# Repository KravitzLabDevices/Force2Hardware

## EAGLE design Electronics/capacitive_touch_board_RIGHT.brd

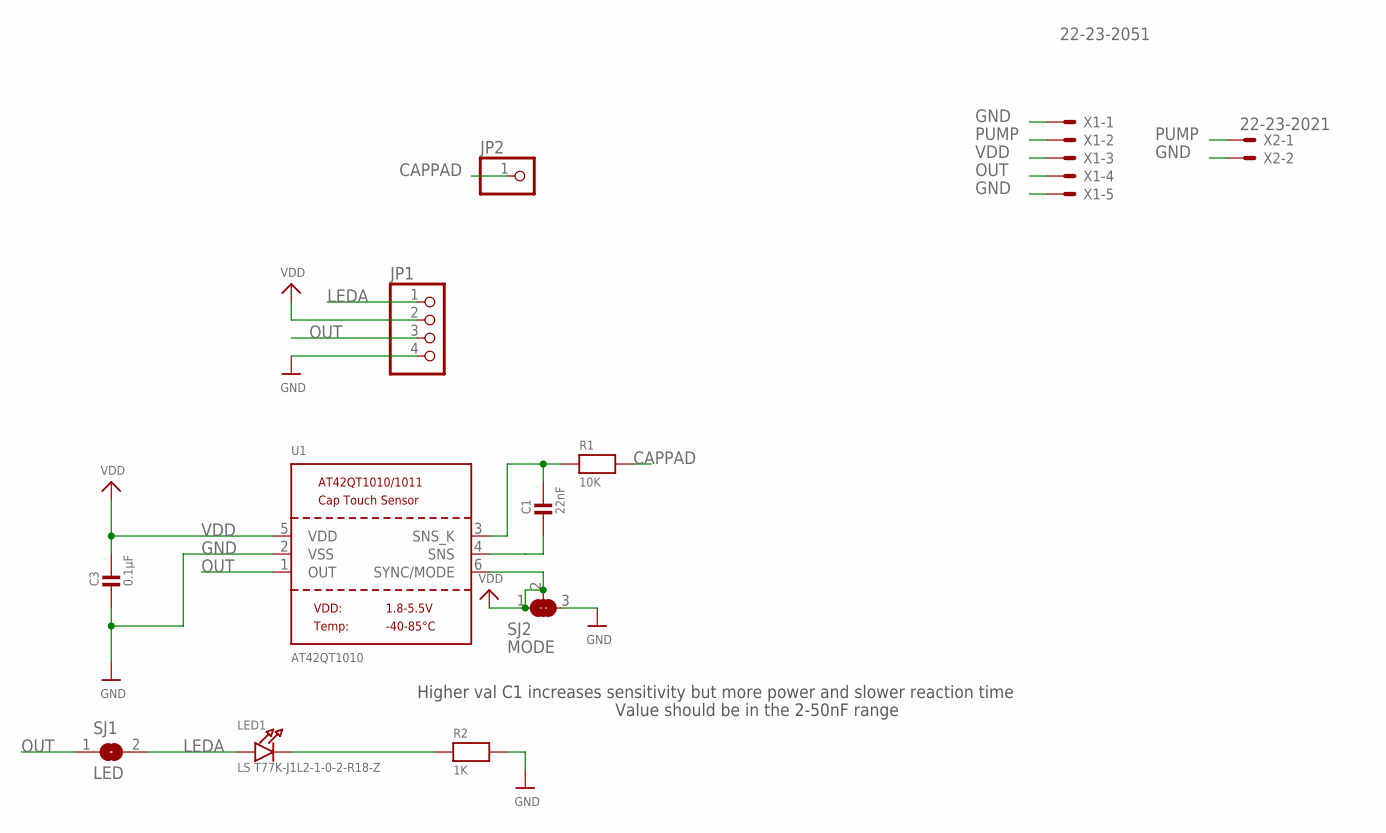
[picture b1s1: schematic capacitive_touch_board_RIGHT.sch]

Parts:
C1: 22nF; _0805
C3: 0.1µF; _0805
JP1: HEADER-1X476MIL; 1X04_ROUND_76
JP2: PINHD-1X1; 1X01
LED1: LS T77K-J1L2-1-0-2-R18-Z; PLCC2_REVMOUNT
R1: 10K; _0805
R2: 1K; _0805
SJ1: LED; SOLDERJUMPER_CLOSEDWIRE
SJ2: MODE; SOLDERJUMPER_2WAY_OPEN_NOPASTE
U1: AT42QT1010; SOT23-6
X1: 22-23-2051
X2: 22-23-2021

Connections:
CAPPAD: JP2.1, R1.2
GND: C3.2, JP1.4, R2.2, SJ2.3, U1.2 (VSS), X1.1, X1.5, X2.2
LEDA: JP1.1, LED1.A, SJ1.2
unnamed: C1.2, U1.4 (SNS)
unnamed: C1.1, R1.1, U1.3 (SNS_K)
unnamed: LED1.K (C), R2.1
OUT: JP1.3, SJ1.1, U1.1 (OUT), X1.4
PUMP: X1.2, X2.1
VDD: C3.1, JP1.2, SJ2.1, SJ2.2, U1.5 (VDD), U1.6 (SYNC/MODE), X1.3

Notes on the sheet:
Higher val C1 increases sensitivity but more power and slower reaction time
Value should be in the 2-50nF range

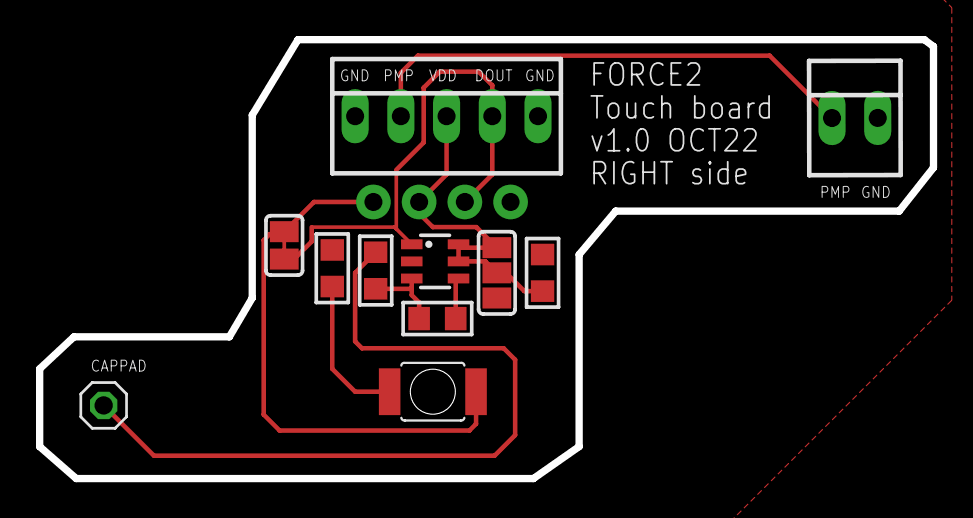
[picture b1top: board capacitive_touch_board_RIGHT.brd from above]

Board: 2 copper layers, 49.7 x 24.4 mm, 12 parts (0 on the bottom side), 9 nets.

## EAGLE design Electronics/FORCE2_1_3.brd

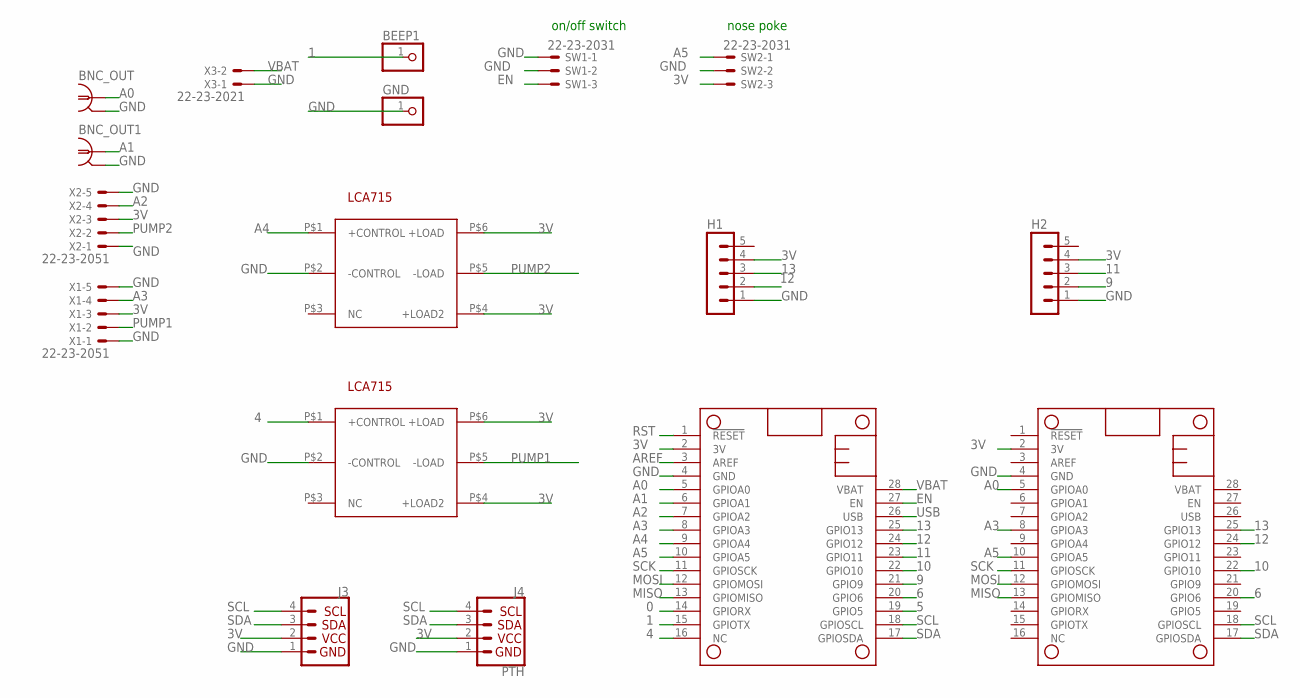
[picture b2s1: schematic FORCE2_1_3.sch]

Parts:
BEEP1: PINHD-1X1; 1X01
BNC_OUT, BNC_OUT1: 1-227161-0; AMP_227161
GND: PINHD-1X1; 1X01
H1, H2: MA05-1
J3: QWIIC_CONNECTORJS-1MM; 1X04_1MM_RA
J4: PTH; 1X04
MS1, MS2: MICROSHIELD_NODIM; MICROSHIELD_DIM
SSR2, SSR3: LCA715S; LCA7XX
SW1, SW2: 22-23-2031
X1, X2: 22-23-2051
X3: 22-23-2021

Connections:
0: MS2.14 (GPIORX)
1: BEEP1.1, MS2.15 (GPIOTX)
3V: H1.4, H2.4, J3.2, J4.2, MS1.2 (3V), MS2.2 (3V), SSR2.P$4 (+LOAD2), SSR2.P$6 (+LOAD), SSR3.P$4 (+LOAD2), SSR3.P$6 (+LOAD), SW2.3, X1.3, X2.3
4: MS2.16 (NC), SSR2.P$1 (+CONTROL)
5: MS2.19 (GPIO5)
6: MS1.20 (GPIO6), MS2.20 (GPIO6)
9: H2.2, MS2.21 (GPIO9)
10: MS1.22 (GPIO10), MS2.22 (GPIO10)
11: H2.3, MS2.23 (GPIO11)
12: H1.2, MS1.24 (GPIO12), MS2.24 (GPIO12)
13: H1.3, MS1.25 (GPIO13), MS2.25 (GPIO13)
A0: BNC_OUT.1, MS1.5 (GPIOA0), MS2.5 (GPIOA0)
A1: BNC_OUT1.1, MS2.6 (GPIOA1)
A2: MS2.7 (GPIOA2), X2.4
A3: MS1.8 (GPIOA3), MS2.8 (GPIOA3), X1.4
A4: MS2.9 (GPIOA4), SSR3.P$1 (+CONTROL)
A5: MS1.10 (GPIOA5), MS2.10 (GPIOA5), SW2.1
AREF: MS2.3 (AREF)
EN: MS2.27 (EN), SW1.3
GND: BNC_OUT.2, BNC_OUT1.2, GND.1, H1.1, H2.1, J3.1, J4.1, MS1.4 (GND), MS2.4 (GND), SSR2.P$2 (-CONTROL), SSR3.P$2 (-CONTROL), SW1.1, SW1.2, SW2.2, X1.1, X1.5, X2.1, X2.5, X3.1
MISO: MS1.13 (GPIOMISO), MS2.13 (GPIOMISO)
MOSI: MS1.12 (GPIOMOSI), MS2.12 (GPIOMOSI)
PUMP1: SSR2.P$5 (-LOAD), X1.2
PUMP2: SSR3.P$5 (-LOAD), X2.2
RST: MS2.1 (!RESET)
SCK: MS1.11 (GPIOSCK), MS2.11 (GPIOSCK)
SCL: J3.4, J4.4, MS1.18 (GPIOSCL), MS2.18 (GPIOSCL)
SDA: J3.3, J4.3, MS1.17 (GPIOSDA), MS2.17 (GPIOSDA)
USB: MS2.26 (USB)
VBAT: MS2.28 (VBAT), X3.2

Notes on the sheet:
nose poke
on/off switch

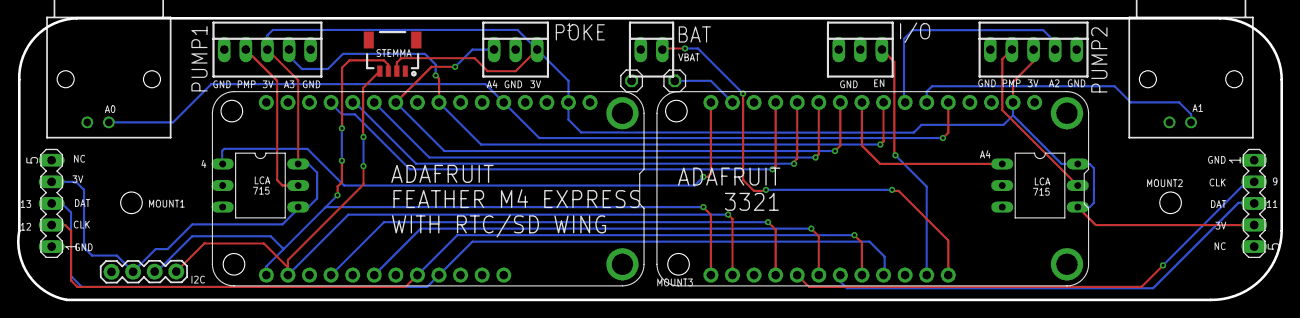
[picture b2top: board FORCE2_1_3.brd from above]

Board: 2 copper layers, 148.7 x 33.1 mm, 17 parts (0 on the bottom side), 25 nets.

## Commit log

2022-10-12 First commit. Added electronics, stl file, and readme

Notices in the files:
parts and their libraries:
SparkFun-Connectors: Licensing: Creative Commons ShareAlike 4.0 International - https://creativecommons.org/licenses/by-sa/4.0
microbuilder: This work is placed in the public domain, and may be freely used for commercial and non-commercial work with the following conditions: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
